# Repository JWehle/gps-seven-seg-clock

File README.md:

# gps-seven-seg-clock
A large seven segment clock that uses highly accurate GPS time.

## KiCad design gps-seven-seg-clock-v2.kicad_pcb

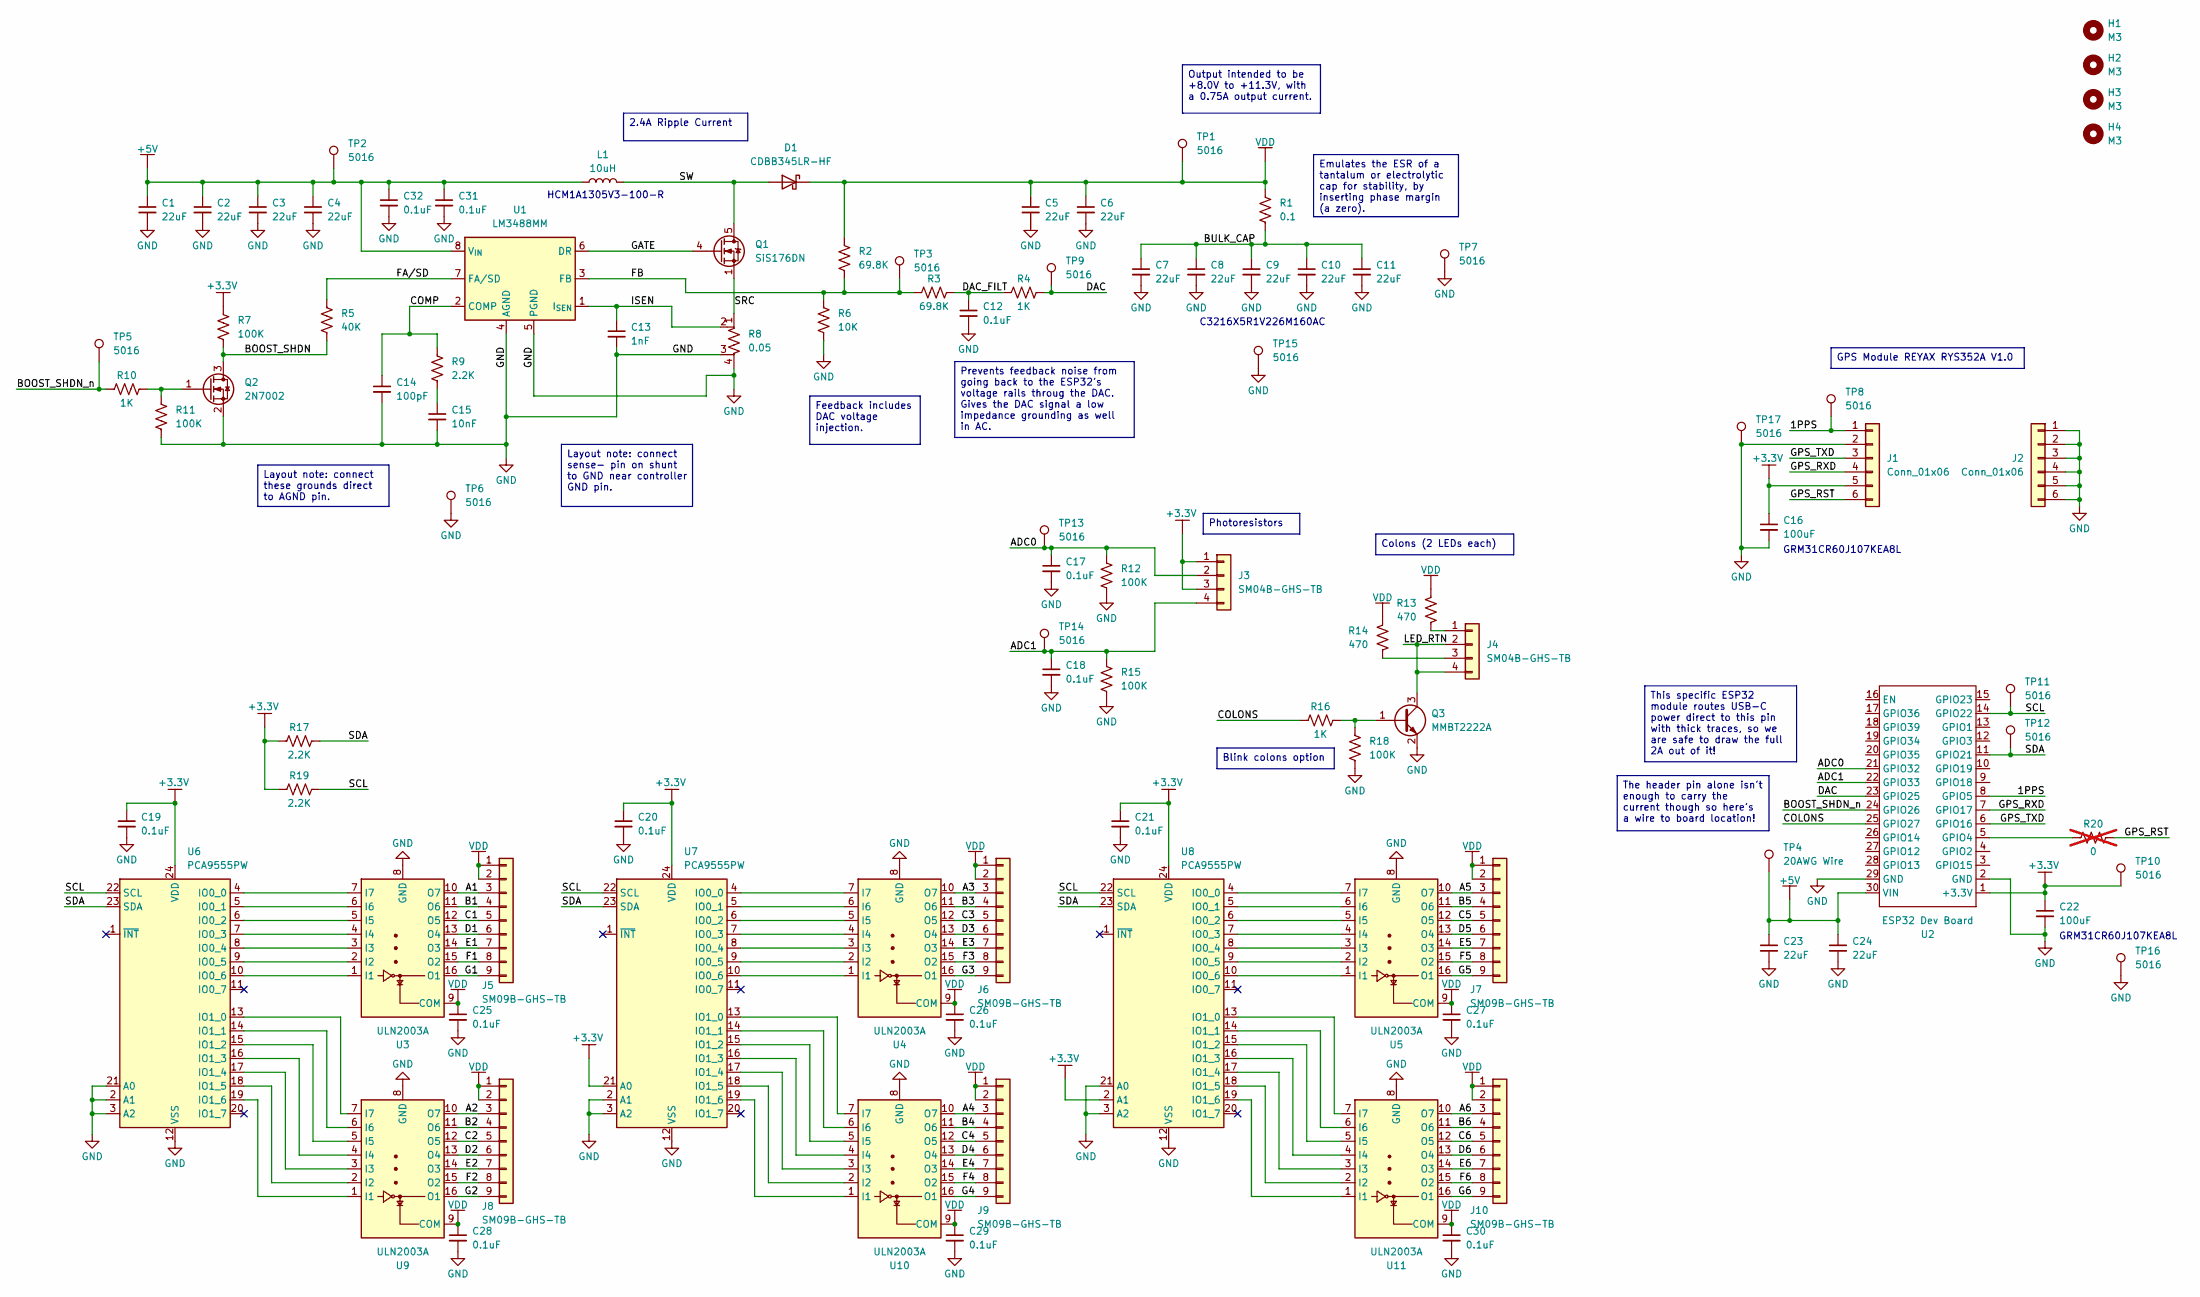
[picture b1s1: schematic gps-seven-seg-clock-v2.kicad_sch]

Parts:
C1, C2, C3, C4, C5, C6, C7, C8, C9, C10, C11, C23, C24: 22uF; C_1206_3216Metric_Pad1.33x1.80mm_HandSolder
C12, C17, C18, C19, C20, C21, C25, C26, C27, C28, C29, C30, C31, C32: 0.1uF; C_0603_1608Metric
C13: 1nF; C_0603_1608Metric
C14: 100pF; C_0603_1608Metric
C15: 10nF; C_0603_1608Metric
C16, C22: 100uF; C_1206_3216Metric_Pad1.33x1.80mm_HandSolder
D1: CDBB345LR-HF; D_SMB
H1, H2, H3, H4: M3; MountingHole_3.2mm_M3
J1, J2: Conn_01x06; PinSocket_1x06_P2.54mm_Vertical
J3, J4: SM04B-GHS-TB; JST_GH_SM04B-GHS-TB_1x04-1MP_P1.25mm_Horizontal
J5, J6, J7, J8, J9, J10: SM09B-GHS-TB; JST_GH_SM09B-GHS-TB_1x09-1MP_P1.25mm_Horizontal
L1: 10uH; L_Sunlord_MWSA1204S-100
Q1: SiS176DN; Vishay_PowerPAK_1212-8_Single
Q2: 2N7002; SOT-23
Q3: MMBT2222A; SOT-23
R1: 0.1; R_1206_3216Metric
R2, R3: 69.8K; R_0603_1608Metric
R4, R10, R16: 1K; R_0603_1608Metric
R5: 40K; R_0603_1608Metric
R6: 10K; R_0603_1608Metric
R7, R11, R12, R15, R18: 100K; R_0603_1608Metric
R8: 0.05; R_Shunt_Vishay_WSK2512_6332Metric_T2.21mm
R9, R17, R19: 2.2K; R_0603_1608Metric
R13, R14: 470; R_1206_3216Metric
R20: 0; R_0603_1608Metric; not fitted
TP1, TP2, TP6, TP7, TP10, TP15, TP16, TP17: 5016; TestPoint_Keystone_5016_Vias
TP3, TP5, TP8, TP9, TP11, TP12, TP13, TP14: 5016; TestPoint_Keystone_5016_Compact
TP4: 20AWG Wire; TestPoint_THTPad_D2.0mm_Drill1.0mm
U1: LM3488MM; VSSOP-8_3x3mm_P0.65mm
U2: ESP32 Dev Board; ESP32_MODULE
U3, U4, U5, U9, U10, U11: ULN2003A; SOIC-16_3.9x9.9mm_P1.27mm
U6, U7, U8: PCA9555PW; TSSOP-24_4.4x7.8mm_P0.65mm

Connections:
+3.3V: C16.1, C19.1, C20.1, C21.1, C22.1, J1.5, J3.1, J3.3, R7.1, R17.1, R19.1, TP10.1, U2.1 (+3.3V), U6.24 (VDD), U7.21 (A0), U7.24 (VDD), U8.2 (A1), U8.24 (VDD)
+5V: C1.1, C2.1, C3.1, C4.1, C23.1, C24.1, C31.1, C32.1, L1.1, TP2.1, TP4.1, U1.8 (V_{IN}), U2.30 (VIN)
/1PPS: J1.1, TP8.1, U2.8 (GPIO5)
/A1: J5.3, U3.10 (O7)
/A2: J8.3, U9.10 (O7)
/A3: J6.3, U4.10 (O7)
/A4: J9.3, U10.10 (O7)
/A5: J7.3, U5.10 (O7)
/A6: J10.3, U11.10 (O7)
/ADC0: C17.1, J3.2, R12.1, TP13.1, U2.21 (GPIO32)
/ADC1: C18.1, J3.4, R15.1, TP14.1, U2.22 (GPIO33)
/B1: J5.4, U3.11 (O6)
/B2: J8.4, U9.11 (O6)
/B3: J6.4, U4.11 (O6)
/B4: J9.4, U10.11 (O6)
/B5: J7.4, U5.11 (O6)
/B6: J10.4, U11.11 (O6)
/BOOST_SHDN: Q2.3 (D), R5.2, R7.2
/BOOST_SHDN_n: R10.1, TP5.1, U2.24 (GPIO26)
/BULK_CAP: C7.1, C8.1, C9.1, C10.1, C11.1, R1.2
/C1: J5.5, U3.12 (O5)
/C2: J8.5, U9.12 (O5)
/C3: J6.5, U4.12 (O5)
/C4: J9.5, U10.12 (O5)
/C5: J7.5, U5.12 (O5)
/C6: J10.5, U11.12 (O5)
/COLONS: R16.1, U2.25 (GPIO27)
/COMP: C14.1, R9.1, U1.2 (COMP)
/D1: J5.6, U3.13 (O4)
/D2: J8.6, U9.13 (O4)
/D3: J6.6, U4.13 (O4)
/D4: J9.6, U10.13 (O4)
/D5: J7.6, U5.13 (O4)
/D6: J10.6, U11.13 (O4)
/DAC: R4.2, TP9.1, U2.23 (GPIO25)
/DAC_FILT: C12.1, R3.2, R4.1
/E1: J5.7, U3.14 (O3)
/E2: J8.7, U9.14 (O3)
/E3: J6.7, U4.14 (O3)
/E4: J9.7, U10.14 (O3)
/E5: J7.7, U5.14 (O3)
/E6: J10.7, U11.14 (O3)
/F1: J5.8, U3.15 (O2)
/F2: J8.8, U9.15 (O2)
/F3: J6.8, U4.15 (O2)
/F4: J9.8, U10.15 (O2)
/F5: J7.8, U5.15 (O2)
/F6: J10.8, U11.15 (O2)
/FA/SD: R5.1, U1.7 (FA/SD)
/FB: R2.2, R3.1, R6.1, TP3.1, U1.3 (FB)
/G1: J5.9, U3.16 (O1)
/G2: J8.9, U9.16 (O1)
/G3: J6.9, U4.16 (O1)
/G4: J9.9, U10.16 (O1)
/G5: J7.9, U5.16 (O1)
/G6: J10.9, U11.16 (O1)
/GATE: Q1.4 (G), U1.6 (DR)
/GPS_RST: J1.6, R20.2
/GPS_RXD: J1.4, U2.7 (GPIO17)
/GPS_TXD: J1.3, U2.6 (GPIO16)
/ISEN: C13.1, R8.2, U1.1 (I_{SEN})
/LED_RTN: J4.2, J4.4, Q3.3 (C)
/SCL: R19.2, TP11.1, U2.14 (GPIO22), U6.22 (SCL), U7.22 (SCL), U8.22 (SCL)
/SDA: R17.2, TP12.1, U2.11 (GPIO21), U6.23 (SDA), U7.23 (SDA), U8.23 (SDA)
/SRC: Q1.1 (S), Q1.2 (S), Q1.3 (S), R8.1
/SW: D1.2 (A), L1.2, Q1.5 (D)
GND: C1.2, C2.2, C3.2, C4.2, C5.2, C6.2, C7.2, C8.2, C9.2, C10.2, C11.2, C12.2, C13.2, C14.2, C15.2, C16.2, C17.2, C18.2, C19.2, C20.2, C21.2, C22.2, C23.2, C24.2, C25.2, C26.2, C27.2, C28.2, C29.2, C30.2, C31.2, C32.2, J1.2, J2.1, J2.2, J2.3, J2.4, J2.5, J2.6, Q2.2 (S), Q3.2 (E), R6.2, R8.3, R8.4, R11.2, R12.2, R15.2, R18.2, TP6.1, TP7.1, TP15.1, TP16.1, TP17.1, U1.4 (AGND), U1.5 (PGND), U2.2 (GND), U2.29 (GND), U3.8 (GND), U4.8 (GND), U5.8 (GND), U6.2 (A1), U6.3 (A2), U6.12 (VSS), U6.21 (A0), U7.2 (A1), U7.3 (A2), U7.12 (VSS), U8.3 (A2), U8.12 (VSS), U8.21 (A0), U9.8 (GND), U10.8 (GND), U11.8 (GND)
unnamed: C15.1, R9.2
unnamed: J4.1, R13.2
unnamed: J4.3, R14.2
unnamed: Q2.1 (G), R10.2, R11.1
unnamed: Q3.1 (B), R16.2, R18.1
unnamed: R20.1, U2.5 (GPIO4)
unnamed: U3.1 (I1), U6.10 (IO0_6)
unnamed: U3.2 (I2), U6.9 (IO0_5)
unnamed: U3.3 (I3), U6.8 (IO0_4)
unnamed: U3.4 (I4), U6.7 (IO0_3)
unnamed: U3.5 (I5), U6.6 (IO0_2)
unnamed: U3.6 (I6), U6.5 (IO0_1)
unnamed: U3.7 (I7), U6.4 (IO0_0)
unnamed: U4.1 (I1), U7.10 (IO0_6)
unnamed: U4.2 (I2), U7.9 (IO0_5)
unnamed: U4.3 (I3), U7.8 (IO0_4)
unnamed: U4.4 (I4), U7.7 (IO0_3)
unnamed: U4.5 (I5), U7.6 (IO0_2)
unnamed: U4.6 (I6), U7.5 (IO0_1)
unnamed: U4.7 (I7), U7.4 (IO0_0)
unnamed: U5.1 (I1), U8.10 (IO0_6)
unnamed: U5.2 (I2), U8.9 (IO0_5)
unnamed: U5.3 (I3), U8.8 (IO0_4)
unnamed: U5.4 (I4), U8.7 (IO0_3)
unnamed: U5.5 (I5), U8.6 (IO0_2)
unnamed: U5.6 (I6), U8.5 (IO0_1)
unnamed: U5.7 (I7), U8.4 (IO0_0)
unnamed: U6.13 (IO1_0), U9.7 (I7)
unnamed: U6.14 (IO1_1), U9.6 (I6)
unnamed: U6.15 (IO1_2), U9.5 (I5)
unnamed: U6.16 (IO1_3), U9.4 (I4)
unnamed: U6.17 (IO1_4), U9.3 (I3)
unnamed: U6.18 (IO1_5), U9.2 (I2)
unnamed: U6.19 (IO1_6), U9.1 (I1)
unnamed: U7.19 (IO1_6), U10.1 (I1)
unnamed: U7.18 (IO1_5), U10.2 (I2)
unnamed: U7.17 (IO1_4), U10.3 (I3)
unnamed: U7.16 (IO1_3), U10.4 (I4)
unnamed: U7.15 (IO1_2), U10.5 (I5)
unnamed: U7.14 (IO1_1), U10.6 (I6)
unnamed: U7.13 (IO1_0), U10.7 (I7)
unnamed: U8.19 (IO1_6), U11.1 (I1)
unnamed: U8.18 (IO1_5), U11.2 (I2)
unnamed: U8.17 (IO1_4), U11.3 (I3)
unnamed: U8.16 (IO1_3), U11.4 (I4)
unnamed: U8.15 (IO1_2), U11.5 (I5)
unnamed: U8.14 (IO1_1), U11.6 (I6)
unnamed: U8.13 (IO1_0), U11.7 (I7)
VDD: C5.1, C6.1, C25.1, C26.1, C27.1, C28.1, C29.1, C30.1, D1.1 (K), J5.1, J5.2, J6.1, J6.2, J7.1, J7.2, J8.1, J8.2, J9.1, J9.2, J10.1, J10.2, R1.1, R2.1, R13.1, R14.1, TP1.1, U3.9 (COM), U4.9 (COM), U5.9 (COM), U9.9 (COM), U10.9 (COM), U11.9 (COM)

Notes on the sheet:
GRM31CR60J107KEA8L
C3216X5R1V226M160AC
HCM1A1305V3-100-R
2.4A Ripple Current
Feedback includes DAC voltage injection.
Photoresistors
The header pin alone isn't enough to carry the current though so here's a wire to board location!
Layout note: connect sense- pin on shunt to GND near controller GND pin.
Blink colons option
GPS Module REYAX RYS352A V1.0
Emulates the ESR of a tantalum or electrolytic cap for stability, by inserting phase margin (a zero).
Colons (2 LEDs each)
Output intended to be +8.0V to +11.3V, with a 0.75A output current.
This specific ESP32 module routes USB-C power direct to this pin with thick traces, so we are safe to draw the full 2A out of it!
Prevents feedback noise from going back to the ESP32's voltage rails throug the DAC. Gives the DAC signal a low impedance grounding as well in AC.
Layout note: connect these grounds direct to AGND pin.

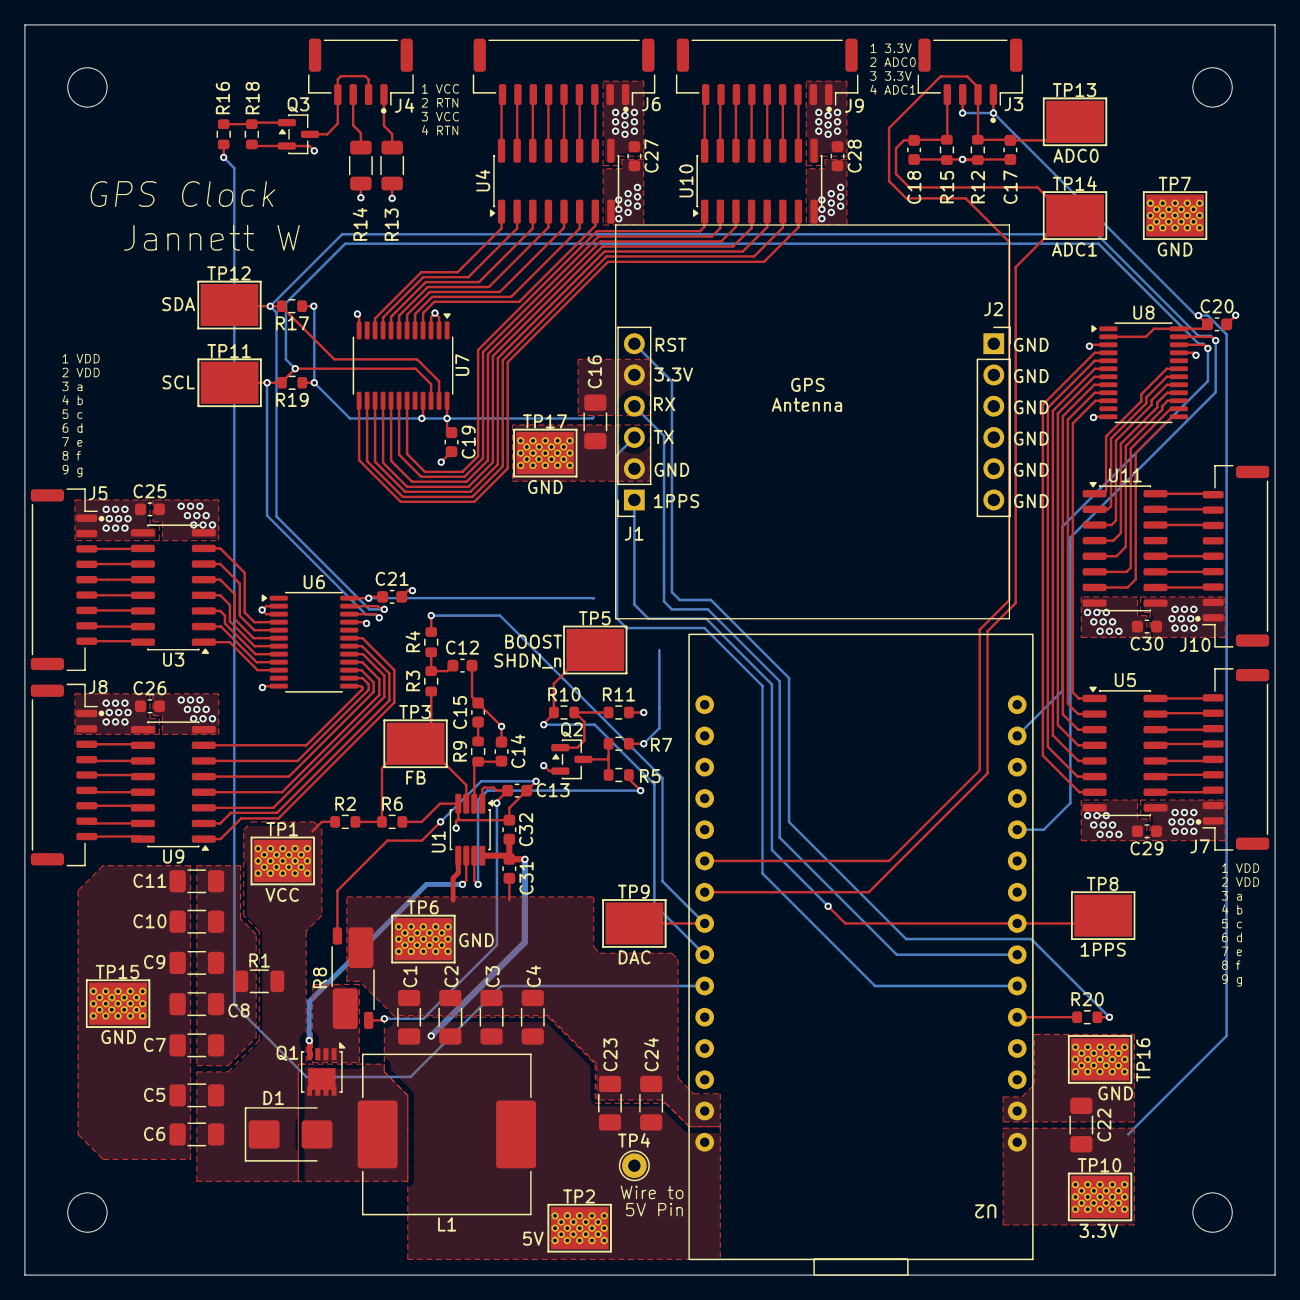
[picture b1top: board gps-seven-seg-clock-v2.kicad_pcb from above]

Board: 4 copper layers, 101.6 x 101.6 mm, 99 parts (0 on the bottom side), 116 nets.

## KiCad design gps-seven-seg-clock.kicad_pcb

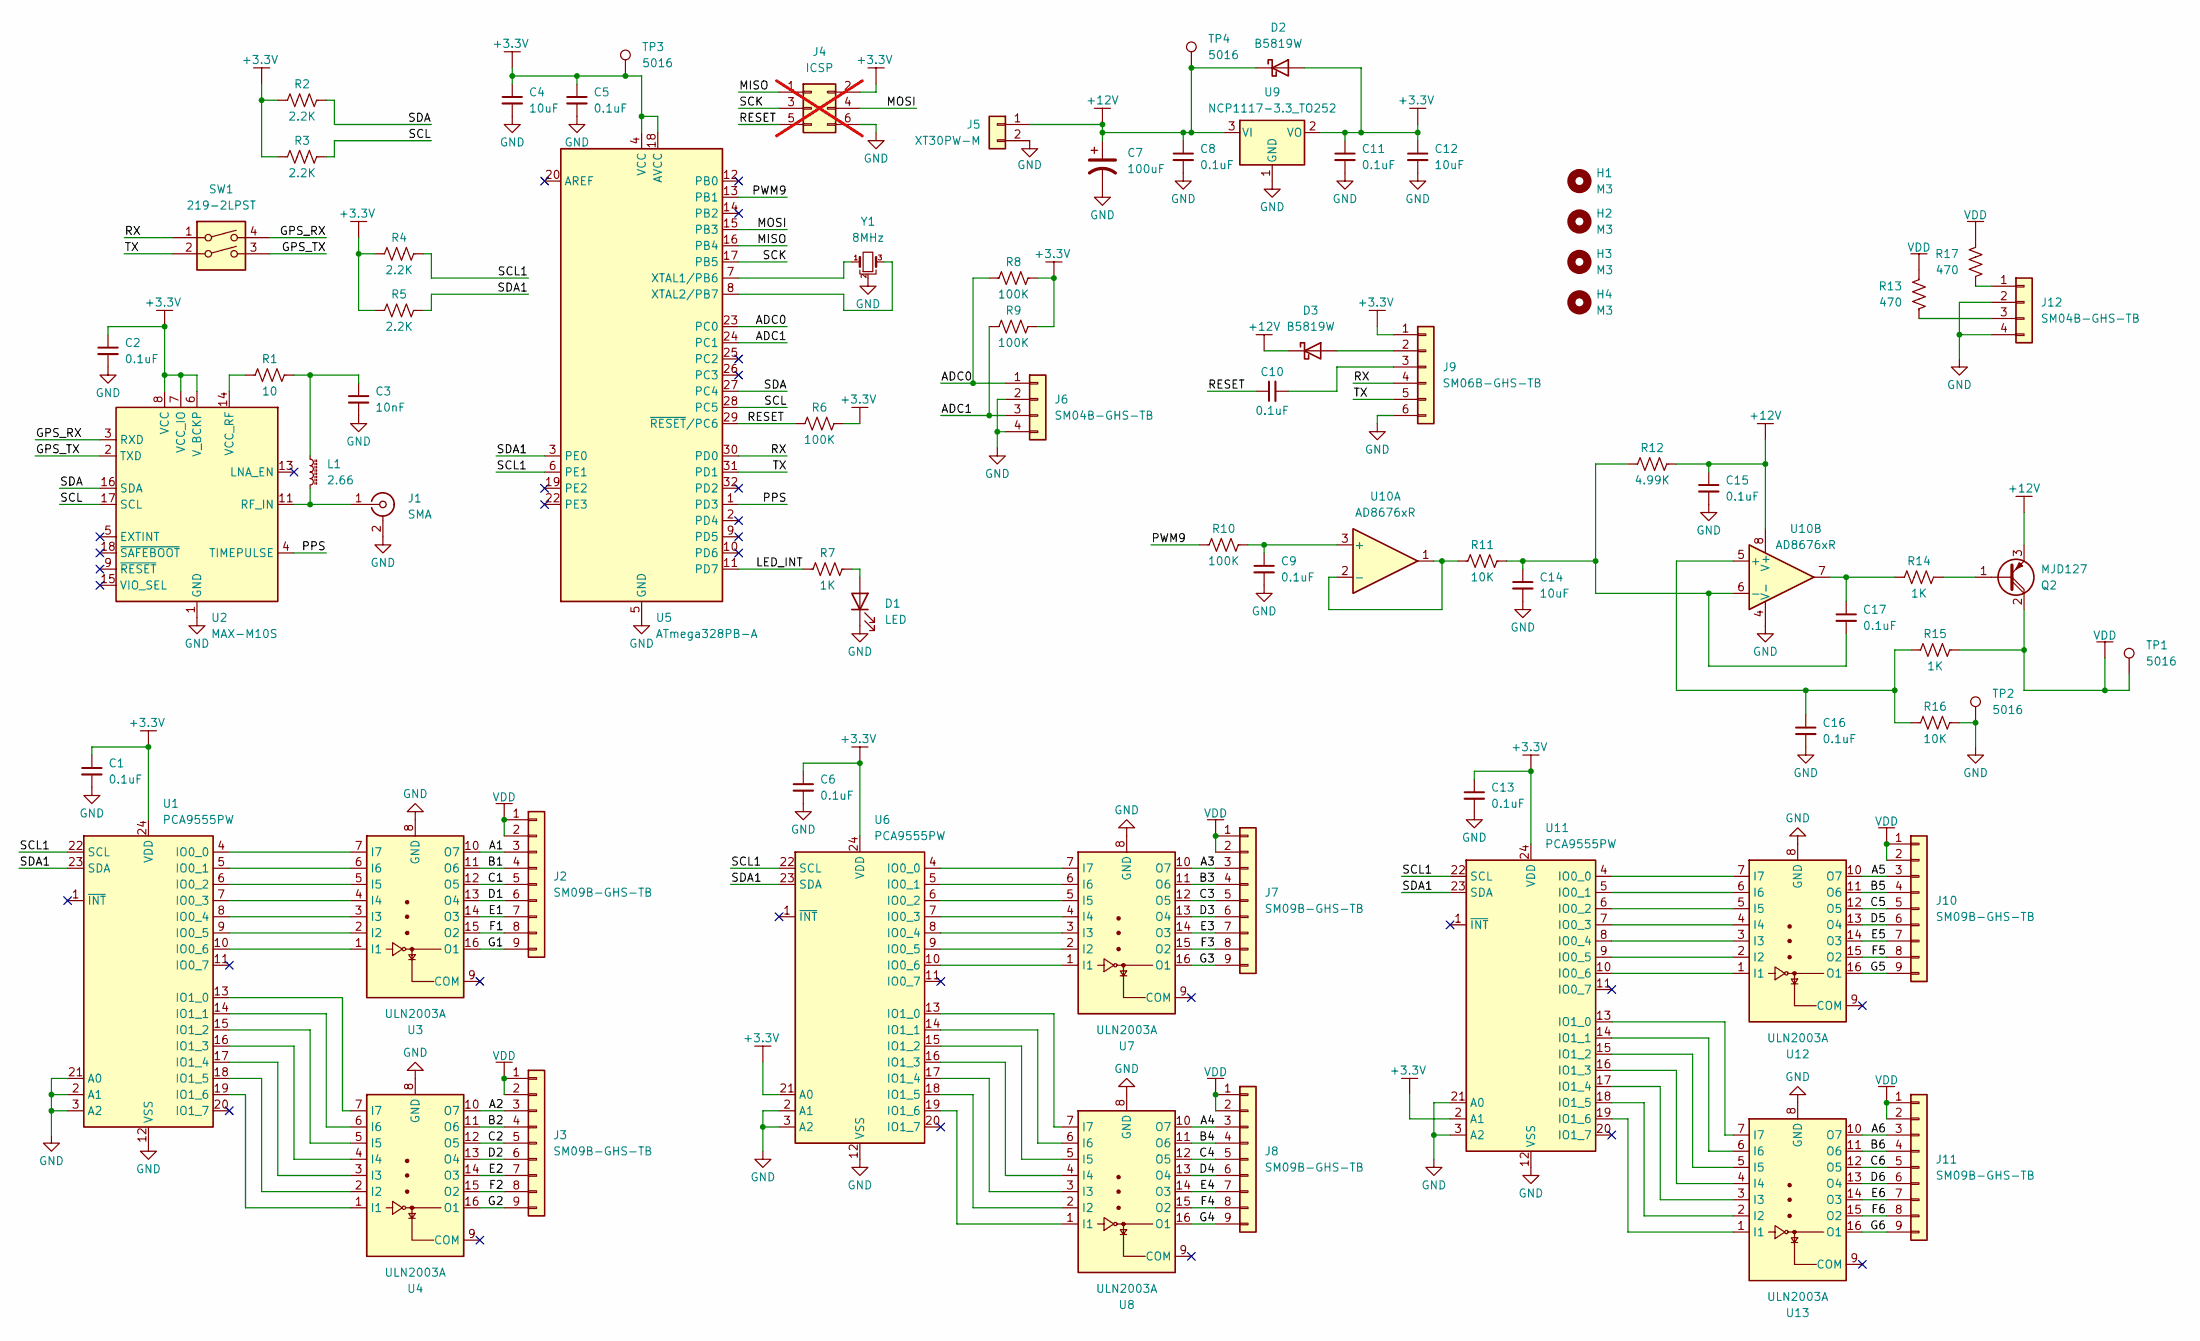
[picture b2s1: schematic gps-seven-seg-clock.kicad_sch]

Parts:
C1, C2, C5, C6, C8, C9, C10, C11, C13, C15, C16, C17: 0.1uF; C_0603_1608Metric
C3: 10nF; C_0603_1608Metric
C4, C12, C14: 10uF; C_0603_1608Metric
C7: 100uF; CP_Elec_6.3x5.4_Nichicon
D1: LED; LED_0603_1608Metric_Pad1.05x0.95mm_HandSolder
D2, D3: B5819W; D_SOD-123
H1, H2, H3, H4: M3; MountingHole_3.2mm_M3
J1: SMA; SMA_Amphenol_132289_EdgeMount
J2, J3, J7, J8, J10, J11: SM09B-GHS-TB; JST_GH_SM09B-GHS-TB_1x09-1MP_P1.25mm_Horizontal
J4: ICSP; PinSocket_2x03_P2.00mm_Vertical; not fitted
J5: XT30PW-M; AMASS_XT30PW-M_1x02_P2.50mm_Horizontal
J6, J12: SM04B-GHS-TB; JST_GH_SM04B-GHS-TB_1x04-1MP_P1.25mm_Horizontal
J9: SM06B-GHS-TB; JST_GH_SM06B-GHS-TB_1x06-1MP_P1.25mm_Horizontal
L1: 2.66; L_0805_2012Metric_Pad1.15x1.40mm_HandSolder
Q2: MJD127; TO-252-2
R1: 10; R_0603_1608Metric
R2, R3, R4, R5: 2.2K; R_0603_1608Metric
R6, R8, R9, R10: 100K; R_0603_1608Metric
R7, R14, R15: 1K; R_0603_1608Metric
R11, R16: 10K; R_0603_1608Metric
R12: 4.99K; R_0603_1608Metric
R13, R17: 470; R_1206_3216Metric
SW1: 219-2LPST; SW_DIP_SPSTx02_Slide_6.7x6.64mm_W8.61mm_P2.54mm_LowProfile
TP1, TP2, TP3, TP4: 5016; TestPoint_Keystone_5016_Vias
U1, U6, U11: PCA9555PW; TSSOP-24_4.4x7.8mm_P0.65mm
U2: MAX-M10S; ublox_MAX
U3, U4, U7, U8, U12, U13: ULN2003A; SOIC-16_3.9x9.9mm_P1.27mm
U5: ATmega328PB-A; TQFP-32_7x7mm_P0.8mm
U9: NCP1117-3.3_TO252; TO-252-2
U10: AD8676xR; SOIC-8_3.9x4.9mm_P1.27mm
Y1: 8MHz; Resonator_SMD_Murata_CSTxExxV-3Pin_3.0x1.1mm_HandSoldering

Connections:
+3.3V: C1.1, C2.1, C4.1, C5.1, C6.1, C11.1, C12.1, C13.1, D2.2 (A), J4.2, J9.1, R2.1, R3.1, R4.1, R5.1, R6.2, R8.2, R9.2, TP3.1, U1.24 (VDD), U2.6 (V_BCKP), U2.7 (VCC_IO), U2.8 (VCC), U5.4 (VCC), U5.18 (AVCC), U6.21 (A0), U6.24 (VDD), U9.2 (VO), U11.2 (A1), U11.24 (VDD)
+12V: C7.1, C8.1, C15.1, D2.1 (K), D3.1 (K), J5.1, Q2.3 (E), R12.2, TP4.1, U9.3 (VI), U10.8 (V+)
/A1: J2.3, U3.10 (O7)
/A2: J3.3, U4.10 (O7)
/A3: J7.3, U7.10 (O7)
/A4: J8.3, U8.10 (O7)
/A5: J10.3, U12.10 (O7)
/A6: J11.3, U13.10 (O7)
/ADC0: J6.1, R8.1, U5.23 (PC0)
/ADC1: J6.3, R9.1, U5.24 (PC1)
/B1: J2.4, U3.11 (O6)
/B2: J3.4, U4.11 (O6)
/B3: J7.4, U7.11 (O6)
/B4: J8.4, U8.11 (O6)
/B5: J10.4, U12.11 (O6)
/B6: J11.4, U13.11 (O6)
/C1: J2.5, U3.12 (O5)
/C2: J3.5, U4.12 (O5)
/C3: J7.5, U7.12 (O5)
/C4: J8.5, U8.12 (O5)
/C5: J10.5, U12.12 (O5)
/C6: J11.5, U13.12 (O5)
/D1: J2.6, U3.13 (O4)
/D2: J3.6, U4.13 (O4)
/D3: J7.6, U7.13 (O4)
/D4: J8.6, U8.13 (O4)
/D5: J10.6, U12.13 (O4)
/D6: J11.6, U13.13 (O4)
/E1: J2.7, U3.14 (O3)
/E2: J3.7, U4.14 (O3)
/E3: J7.7, U7.14 (O3)
/E4: J8.7, U8.14 (O3)
/E5: J10.7, U12.14 (O3)
/E6: J11.7, U13.14 (O3)
/F1: J2.8, U3.15 (O2)
/F2: J3.8, U4.15 (O2)
/F3: J7.8, U7.15 (O2)
/F4: J8.8, U8.15 (O2)
/F5: J10.8, U12.15 (O2)
/F6: J11.8, U13.15 (O2)
/G1: J2.9, U3.16 (O1)
/G2: J3.9, U4.16 (O1)
/G3: J7.9, U7.16 (O1)
/G4: J8.9, U8.16 (O1)
/G5: J10.9, U12.16 (O1)
/G6: J11.9, U13.16 (O1)
/GPS_RX: SW1.4, U2.3 (RXD)
/GPS_TX: SW1.3, U2.2 (TXD)
/LED_INT: R7.1, U5.11 (PD7)
/MISO: J4.1, U5.16 (PB4)
/MOSI: J4.4, U5.15 (PB3)
/PPS: U2.4 (TIMEPULSE), U5.1 (PD3)
/PWM9: R10.1, U5.13 (PB1)
/RESET: C10.1, J4.5, R6.1, U5.29 (~RESET/PC6)
/RX: J9.4, SW1.1, U5.30 (PD0)
/SCK: J4.3, U5.17 (PB5)
/SCL: R3.2, U2.17 (SCL), U5.28 (PC5)
/SCL1: R4.2, U1.22 (SCL), U5.6 (PE1), U6.22 (SCL), U11.22 (SCL)
/SDA: R2.2, U2.16 (SDA), U5.27 (PC4)
/SDA1: R5.2, U1.23 (SDA), U5.3 (PE0), U6.23 (SDA), U11.23 (SDA)
/TX: J9.5, SW1.2, U5.31 (PD1)
GND: C1.2, C2.2, C3.2, C4.2, C5.2, C6.2, C7.2, C8.2, C9.2, C11.2, C12.2, C13.2, C14.2, C15.2, C16.2, D1.1 (K), J1.2 (Ext), J4.6, J5.2, J6.2, J6.4, J9.6, J12.2, J12.4, R16.2, TP2.1, U1.2 (A1), U1.3 (A2), U1.12 (VSS), U1.21 (A0), U2.1 (GND), U2.10 (GND), U2.12 (GND), U3.8 (GND), U4.8 (GND), U5.5 (GND), U5.21 (GND), U6.2 (A1), U6.3 (A2), U6.12 (VSS), U7.8 (GND), U8.8 (GND), U9.1 (GND), U10.4 (V-), U11.3 (A2), U11.12 (VSS), U11.21 (A0), U12.8 (GND), U13.8 (GND), Y1.2
unnamed: C3.1, L1.1, R1.2
unnamed: C17.1, R14.1, U10.7
unnamed: D1.2 (A), R7.2
unnamed: D3.2 (A), J9.2
unnamed: J1.1 (In), L1.2, U2.11 (RF_IN)
unnamed: C10.2, J9.3
unnamed: J12.1, R17.2
unnamed: J12.3, R13.2
unnamed: Q2.1 (B), R14.2
unnamed: U1.4 (IO0_0), U3.7 (I7)
unnamed: U1.5 (IO0_1), U3.6 (I6)
unnamed: U1.6 (IO0_2), U3.5 (I5)
unnamed: U1.7 (IO0_3), U3.4 (I4)
unnamed: U1.8 (IO0_4), U3.3 (I3)
unnamed: U1.9 (IO0_5), U3.2 (I2)
unnamed: U1.10 (IO0_6), U3.1 (I1)
unnamed: U1.13 (IO1_0), U4.7 (I7)
unnamed: U1.14 (IO1_1), U4.6 (I6)
unnamed: U1.15 (IO1_2), U4.5 (I5)
unnamed: U1.16 (IO1_3), U4.4 (I4)
unnamed: U1.17 (IO1_4), U4.3 (I3)
unnamed: U1.18 (IO1_5), U4.2 (I2)
unnamed: U1.19 (IO1_6), U4.1 (I1)
unnamed: R1.1, U2.14 (VCC_RF)
unnamed: U5.7 (XTAL1/PB6), Y1.1
unnamed: U5.8 (XTAL2/PB7), Y1.3
unnamed: U6.4 (IO0_0), U7.7 (I7)
unnamed: U6.5 (IO0_1), U7.6 (I6)
unnamed: U6.6 (IO0_2), U7.5 (I5)
unnamed: U6.7 (IO0_3), U7.4 (I4)
unnamed: U6.8 (IO0_4), U7.3 (I3)
unnamed: U6.9 (IO0_5), U7.2 (I2)
unnamed: U6.10 (IO0_6), U7.1 (I1)
unnamed: U6.13 (IO1_0), U8.7 (I7)
unnamed: U6.14 (IO1_1), U8.6 (I6)
unnamed: U6.15 (IO1_2), U8.5 (I5)
unnamed: U6.16 (IO1_3), U8.4 (I4)
unnamed: U6.17 (IO1_4), U8.3 (I3)
unnamed: U6.18 (IO1_5), U8.2 (I2)
unnamed: U6.19 (IO1_6), U8.1 (I1)
unnamed: C9.1, R10.2, U10.3 (+)
unnamed: R11.1, U10.1, U10.2 (-)
unnamed: C16.1, R15.1, R16.1, U10.5 (+)
unnamed: C14.1, C17.2, R11.2, R12.1, U10.6 (-)
unnamed: U11.4 (IO0_0), U12.7 (I7)
unnamed: U11.5 (IO0_1), U12.6 (I6)
unnamed: U11.6 (IO0_2), U12.5 (I5)
unnamed: U11.7 (IO0_3), U12.4 (I4)
unnamed: U11.8 (IO0_4), U12.3 (I3)
unnamed: U11.9 (IO0_5), U12.2 (I2)
unnamed: U11.10 (IO0_6), U12.1 (I1)
unnamed: U11.13 (IO1_0), U13.7 (I7)
unnamed: U11.14 (IO1_1), U13.6 (I6)
unnamed: U11.15 (IO1_2), U13.5 (I5)
unnamed: U11.16 (IO1_3), U13.4 (I4)
unnamed: U11.17 (IO1_4), U13.3 (I3)
unnamed: U11.18 (IO1_5), U13.2 (I2)
unnamed: U11.19 (IO1_6), U13.1 (I1)
VDD: J2.1, J2.2, J3.1, J3.2, J7.1, J7.2, J8.1, J8.2, J10.1, J10.2, J11.1, J11.2, Q2.2 (C), R13.1, R15.2, R17.1, TP1.1

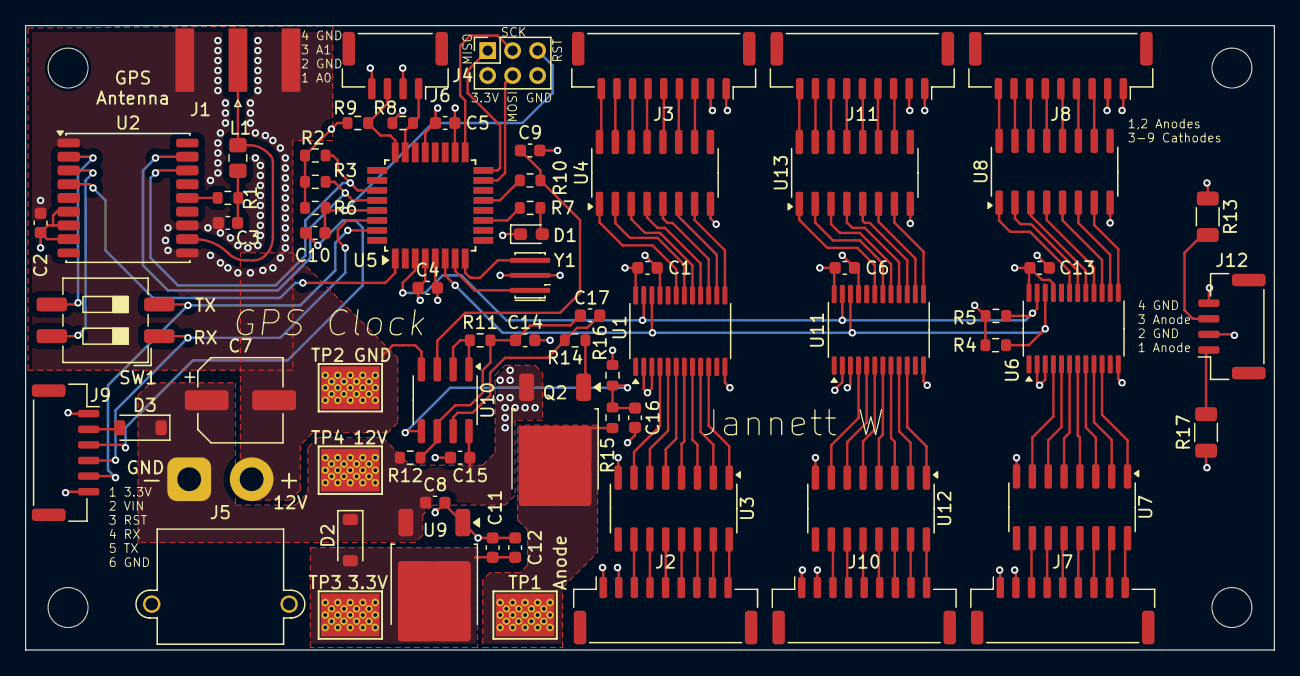
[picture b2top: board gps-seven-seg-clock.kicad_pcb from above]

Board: 4 copper layers, 100.0 x 50.0 mm, 74 parts (0 on the bottom side), 121 nets.

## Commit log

2025-06-16 start
2025-06-26 finished
2025-08-18 bom edits
2026-02-20 schematic v2
2026-02-22 sch and layout
2026-02-23 layout
2026-03-17 gerbers and layout done
